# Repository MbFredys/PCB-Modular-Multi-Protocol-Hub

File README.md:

# ⚡ Universal Smart-Home Modular Hub  

A compact, scalable, multi-protocol communication platform designed for modern smart homes.  
Built around a powerful **ESP32-S3**, with plug-in radio modules for Zigbee/Thread and Proprietary RF.  
Reliable power architecture, clean RF design, and automatic module detection.

---

## 🌍 Overview  
This system uses a **three-board modular hub architecture**:

### **1) Main Board – ESP32-S3 Controller**
Contains the ESP32-S3 with native **Wi-Fi + Bluetooth LE**, full power management, Ethernet support, and the universal expansion bus.

### **2) Zigbee/Thread Module – EFR32MG24**
A dedicated 2.4 GHz radio module supporting **Zigbee**, **Thread**, and **Matter over Thread** with a high-efficiency antenna.

### **3) Proprietary RF Module – nRF24L01+**
A flexible low-power 2.4 GHz module for **custom protocols**, legacy devices, and private links.

⚠️ **Only one expansion module is active at a time.**  
The **Main Board can run standalone** using Wi-Fi and BLE even with no module attached.

---

## 🎯 Problem This Project Solves  
Most smart-home hubs are:

- Locked to one brand or protocol  
- Difficult to expand  
- Closed hardware  
- Not modifiable or repairable  
- Dependent on cloud services  
- Not designed for RF noise isolation  

This project solves these issues with a fully documented, open, modular, serviceable platform.

---

# 🚀 Main Features

---

## 🧠 Main Board – ESP32-S3 Core Controller  

### **Capabilities**
- Native Wi-Fi + BLE  
- USB programming  
- JTAG debugging  
- I²C bus for module identification  
- SPI bus shared with expansion modules  
- Presence-detect signal  
- Ethernet PHY  
- Local battery backup  
- Clean, isolated power rails  

### **Standalone Operation**
If no radio module is plugged in, the board still supports:

- Wi-Fi control  
- BLE provisioning  
- Local automation  
- OTA updates  

---

## 📡 Zigbee / Thread / Matter Module – EFR32MG24  

### **Capabilities**
- Zigbee 3.0  
- Thread 1.3  
- Matter over Thread  
- High-efficiency chip antenna or external u.FL  
- SPI + IRQ communication  
- Local low-noise LDO  
- EEPROM with module ID  
- Hardware reset & enable control  
- SWD header for development  

### **Why a Separate Board?**
- RF noise isolation  
- Easy upgrades  
- Thermal and EMI improvements  
- Lower main-board complexity  

---

## 📡 Proprietary RF Module – nRF24L01+  

### **Capabilities**
- 2.4 GHz bidirectional transceiver  
- SPI interface  
- IRQ line  
- CE line for TX/RX control  
- Local LDO for clean RF power  
- On-board EEPROM for identification  

### **Why It Exists**
- Legacy systems  
- Private, encrypted links  
- Ultra-low-power sensors  
- Custom protocols  

---

# 🔋 Power Architecture

### **Main Board**
- 12 V input  
- Step-down to 5 V  
- 3.3 V LDO for logic  
- Local LDOs for each RF module  
- Battery charger & backup  
- Inrush, surge, ESD protection  
- Proper decoupling everywhere  

### **Radio Modules**
- Dedicated LDO  
- Ferrite-bead power filtering  
- Enable pin for power control  
- RF-clean power domain  

---

# 🧩 Automatic Module Identification (EEPROM)

Every expansion module includes a **24AA02E48 EEPROM** that stores:

- Unique EUI-48  
- Module type ID  

The ESP32 reads the EEPROM via I²C on boot and:

1. Identifies the module type  
2. Powers only the selected module  
3. Loads the appropriate firmware configuration  

---

# 🛡️ Reliability & Safety

- TVS on power rails  
- ESD protection on connectors  
- Solid ground planes  
- RF-clean routing  
- Ferrite-bead domain separation  
- Reverse-polarity protection  
- Controlled RF impedance paths  

---

# 🧭 Why This Architecture Is Better

- **Fully modular** — plug-in radio modules  
- **Upgradable** — replace modules anytime  
- **Main board works standalone**  
- **Automatic detection** via EEPROM  
- **Clean RF design** with isolated power  
- **Open hardware**  
- **Supports Wi-Fi, BLE, Zigbee, Thread, Matter, Proprietary RF**  
- **Future-proof** platform  
- **Easy to manufacture & repair**  

---

# 🛠️ Usage

1. Power the Main Board with 12 V  
2. Plug in a Zigbee or Proprietary RF module  
3. Firmware reads the module EEPROM  
4. Selected module is powered via EN_LDO  
5. ESP32 configures SPI/I²C pins  
6. Start using the hub via Wi-Fi, BLE, or RF  

---

# 🚀 Getting Started

1. Download design files  
2. Open schematic and PCB in KiCad  
3. Review:
   - Power sections  
   - Module connector  
   - RF networks  
   - Decoupling and filtering  
4. Manufacture PCBs  
5. Assembly order:
   1. Power stage  
   2. ESP32-S3 main board  
   3. Expansion connectors  
   4. RF module components  
   5. Antennas  
6. Flash the ESP32-S3 via USB  
7. Flash EFR32 module via SWD (if needed)  
8. Test and integrate with your smart-home backend  

---

# 🪪 License  
This project is licensed under the CERN Open Hardware Licence Version 2 - Weakly Reciprocal (CERN-OHL-W-2.0).
See the [CERN-OHL-W-2.0 ↗](https://gitlab.com/ohwr/project/cernohl/-/wikis/uploads/82b567f43ce515395f7ddbfbad7a8806/cern_ohl_w_v2.txt) file for more information.

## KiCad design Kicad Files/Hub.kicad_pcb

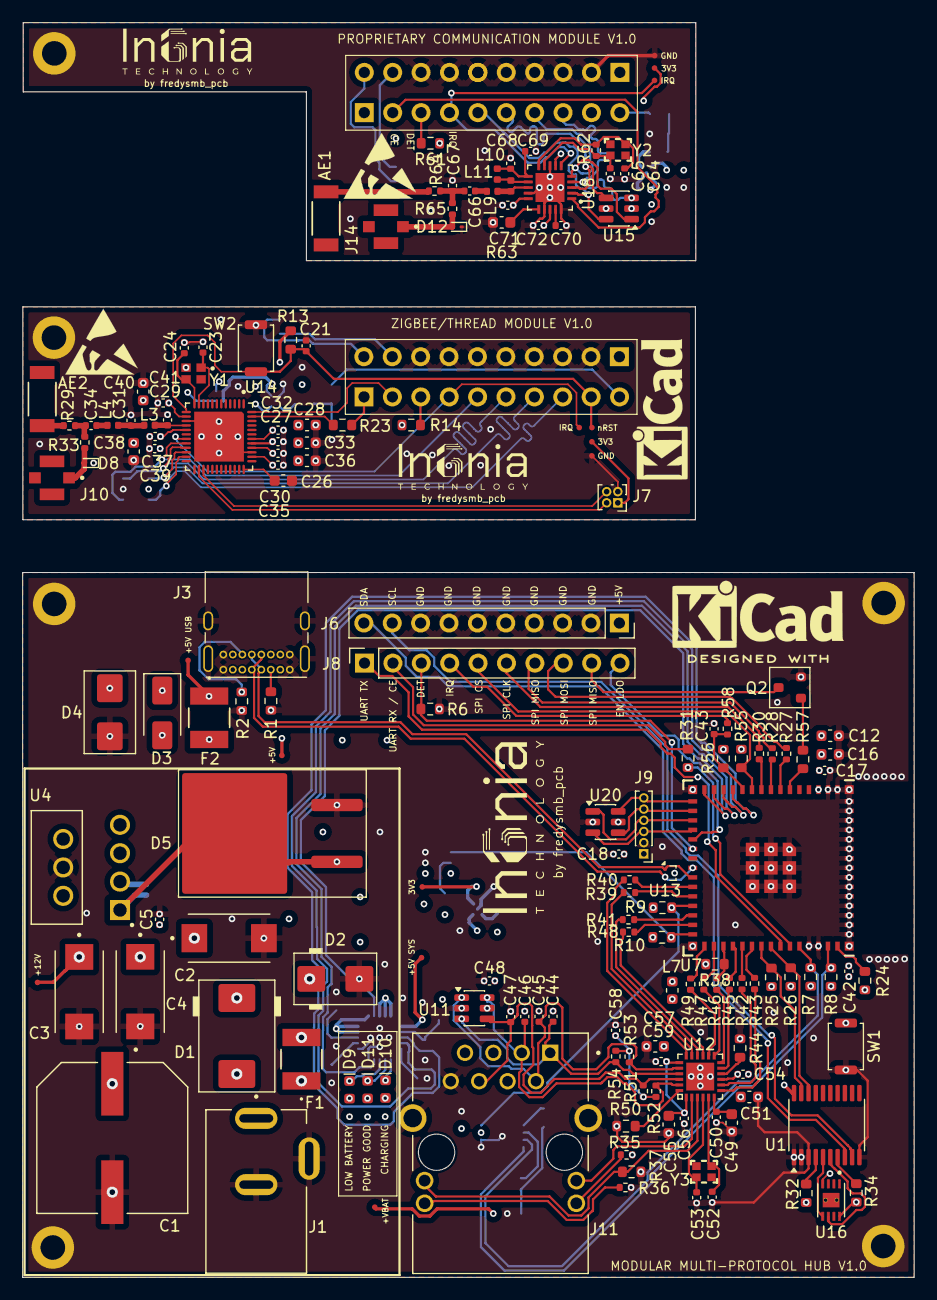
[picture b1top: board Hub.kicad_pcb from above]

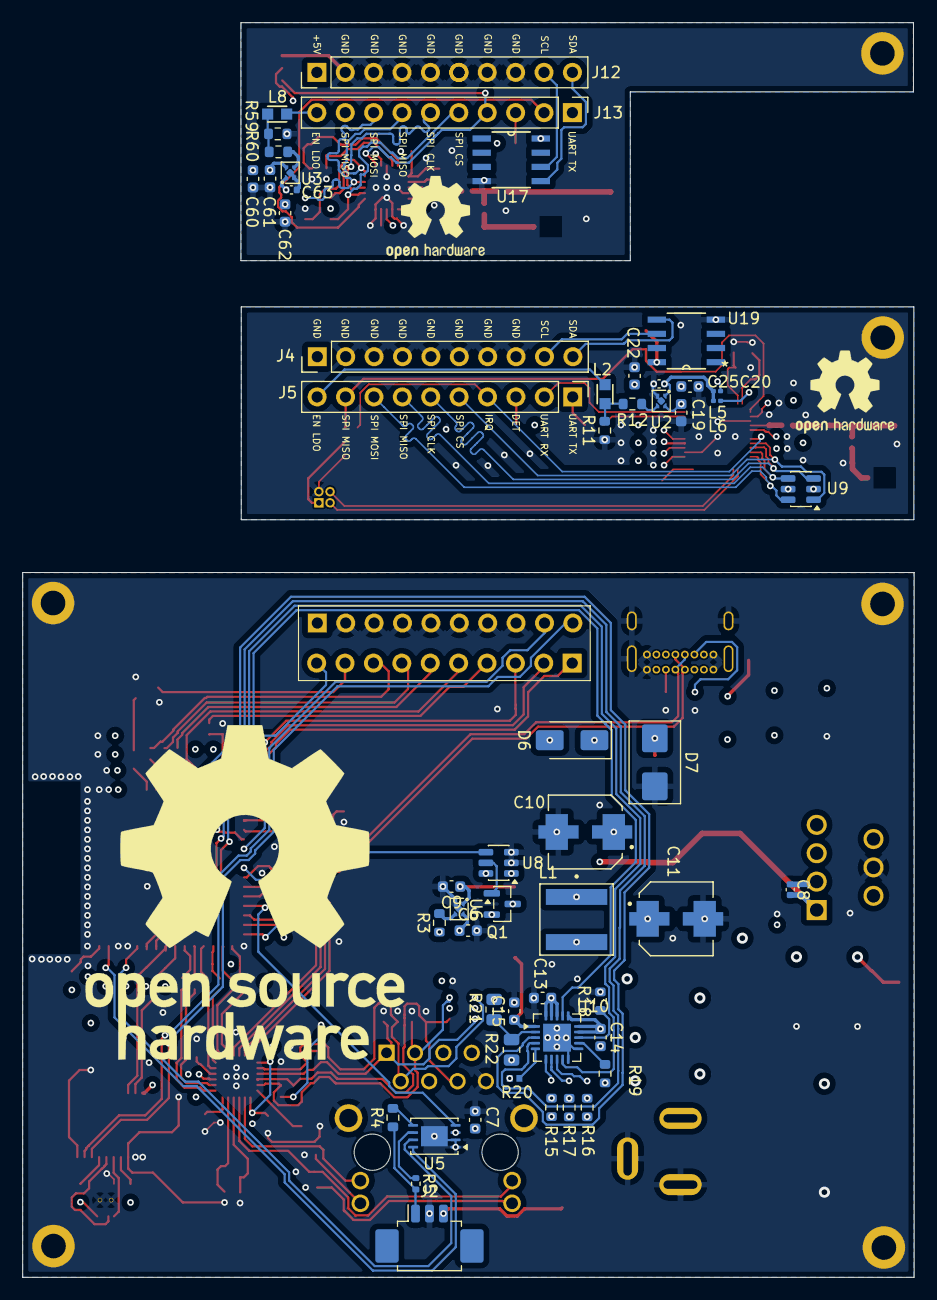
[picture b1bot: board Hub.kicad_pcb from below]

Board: 4 copper layers, 79.7 x 112.2 mm, 218 parts (54 on the bottom side), 159 nets.

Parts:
3V3, 3V3#2, 3V3#3: 0.5mm; TestPoint-0.5mm
+5V, +5V SYS, +5V USB, +12V: 0.5mm; TestPoint-0.5mm
+VBAT: 0.5mm; TestPoint-0.5mm
AE1, AE2: 2450AT42A100E; ANT_2450AT42A100E_JOT
C1: 1000uF; CAP_EEVFK1E102Q
C2, C3, C4: 15uF; CAPPM7343X310N
C5, C37: 0.47uF; C_0402_1005Metric
C6, C7, C9, C13, C16, C20, C22, C26, C28, C33, C36, C38, C49, C55, C57, C61, C62: 1uF; C_0603_1608Metric
C8: 0.01uF; C_0402_1005Metric
C10, C11: 180uF; CAP_EEEFNE181XUV
C12, C19, C51, C60: 10uF; C_0603_1608Metric
C14, C15: 4.7uF; C_0603_1608Metric
C17, C18, C21, C25, C27, C30, C32, C42, C43, C48, C54, C58, C63: 0.1uF; C_0402_1005Metric
C23, C24, C44, C45, C46, C47, C52, C53: 10pF; C_0402_1005Metric
C29: 2.3pF; C_0402_1005Metric
C31: 1.6pF; C_0402_1005Metric
C34, C41: 18pF; C_0402_1005Metric
C35, C69, C71: 10nF; C_0402_1005Metric
C39: 120pF; C_0402_1005Metric
C40: 2.2uF; C_0603_1608Metric
C50, C56, C59: 470pF; C_0402_1005Metric
C64, C65: 22pF; C_0402_1005Metric
C66: 1.5pF; C_0402_1005Metric
C67: 1pF; C_0402_1005Metric
C68, C70: 33nF; C_0402_1005Metric
C72: 1nF; C_0402_1005Metric
D1: SS54; D_SMC
D2: SMBJ12A; D_SMB
D3, D6: SS14; D_SMA
D4, D7: SMBJ5.0CA; D_SMB_TVS
D5: MBRB735; TO-263-2_TabPin1
D8, D12: ESD9B3.3ST5G; D_SOD-923
D9, D10, D11: LEDs; LED_0603_1608Metric
F1, F2: PTC_FUSE; FUSE_1812L05060_LTF
GND: 0.5mm; TestPoint-0.5mm
GND#2: 0.5mm; TestPoint-0.5mm
IRQ: 0.5mm; TestPoint-0.5mm
IRQ#2: 0.5mm; TestPoint-0.5mm
J1: CON_12VDC_IN; MPD_EJ503A
J2: Conn_BAT; Molex_PicoBlade_53261-0371_1x03-1MP_P1.25mm_Horizontal
J3: Conn_USB_C; USB_C_Receptacle_GCT_USB4085
J4, J5, J12, J13: PINHD; PinHeader_1x10_P2.54mm_Vertical
J6, J8: PINHD; PinSocket_1x10_P2.54mm_Vertical
J7: PINHD; PinHeader_2x02_P1.00mm_Vertical
J9: JTAG; PinHeader_1x06_P1.00mm_Vertical
J10, J14: CONMHF1; LINX_CONMHF1-SMD-G-T
J11: ARJM11D7-009-AB-EW2; ABRACON_ARJM11D7-009-AB-EW2
L1: 22uH; IND_XAL6060-223MEB
L2, L8: FerriteBead_0603_1.5A; R_0603
L3: 2.5nH; L_0402_1005Metric
L4: 1.7nH; L_0402_1005Metric
L5, L6: FerriteBead_0603_1.5A; R_0201_0603Metric
L7: FerriteBead; L_0603_1608Metric
L9: 3.9nH; L_0402_1005Metric
L10: 8.2nH; L_0402_1005Metric
L11: 2.7nH; L_0402_1005Metric
Q1: FDN340P; SOT-23
Q2: BC817; SOT-23
R1, R2: 5.1k; R_0603_1608Metric
R3, R6, R11, R59: 100k; R_0603_1608Metric
R4, R8, R9, R10, R12, R13, R14, R24, R37, R44, R55, R56, R57, R60, R61: 10k; R_0603_1608Metric
R5, R58: 100; R_0402_1005Metric
R7, R15, R16, R17, R18, R19: 470k; R_0603_1608Metric
R20: 10k; THRMC1005X55N
R21: 330k; R_0805_2012Metric
R22: 110k; R_0805_2012Metric
R23, R31: 1K; R_0603_1608Metric
R25, R26, R32, R34: 4.7k; R_0603_1608Metric
R27, R28, R30: 22; R_0402_1005Metric
R29, R33, R64, R65: 0; R_0402_1005Metric
R35, R36: 270; R_0402_1005Metric
R38: 2.2k; R_0603_1608Metric
R39, R40, R41, R42, R43, R45, R46, R47, R48, R49: 33; R_0402_1005Metric
R50: 12.1k; R_0603_1608Metric
R51, R52, R53, R54: 50; R_0402_1005Metric
R62: 1M; R_0402_1005Metric
R63: 22k; C_0603_1608Metric
SW1, SW2: uC_Reset; SW_Push_SPST_NO_Alps_SKRK
U1: TCA9544A; TSSOP-20_4.4x6.5mm_P0.65mm
U2, U3, U6: TPS7A20xxxDQN; Texas_X2SON-4_1x1mm_P0.65mm
U4: LM2678T-ADJ; TO127P1041X469X2199-7N
U5: LC709203FQH-01TWG; WDFN-8-1EP_4x3mm_P0.65mm_EP2.4x1.8mm
U7: ESP32-S3-MINI-1; ESP32-MINI
U8: LTC4412xS6; TSOT-23-6
U9, U11, U15, U20: WE-TVS-824015043; SOT-23-6
U10: MCP73871; QFN-20-1EP_4x4mm_P0.5mm_EP2.5x2.5mm
U12: LAN8720A
U13: TPD2EUSB30A; Texas_DRT-3
U14: EFR32MG24B310F1536IM48-B; XCVR_EFR32MG24B310F1536IM48-B
U16: ATECC608A-MAHDA-T; SON50P200X300X60-9N
U17, U19: 24AA02E48-I_SN; SOIC127P600X175-8N
U18: NRF24L01; QFN50P400X400X95-21N
Y1: 39MHz; XTAL_ECS-390-CDX-1932
Y2: 16MHz; Crystal_SMD_2.0x1.6mm
Y3: 25MHz; Crystal_SMD_2.0x1.6mm
nRST: 0.5mm; TestPoint-0.5mm

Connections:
+3V3_Main: 3V3#3.1, C9.1, C12.2, C16.1, C17.2, C18.2, C42.2, C48.2, C51.2, C54.2, J9.1, J11.4 (CT1), J11.5 (CT2), L7.1, R7.1, R8.1, R9.1, R10.1, R24.2, R25.1, R26.1, R32.1, R34.1, R38.2, R55.2, R56.2, SW1.2, U1.20 (VCC), U6.1 (OUT), U7.3 (3V3), U11.5 (VBUS), U12.9 (VDDIO), U16.8 (VCC), U20.5 (VBUS)
+3V3_PROP: 3V3.1, C62.1, C63.2, C71.2, C72.2, R61.1, U3.1 (OUT), U15.5 (VBUS), U17.8 (VCC), U18.7 (VDD), U18.15 (VDD), U18.18 (VDD)
+3V3_ZGB: 3V3#2.1, C22.1, C25.2, C27.2, C28.1, C30.2, C32.2, C33.1, C35.2, C36.1, J7.1, L5.1, L6.1, R13.1, R14.1, U2.1 (OUT), U9.5 (VBUS), U14.38 (VREGVDD), U14.40 (DVDD), U14.41 (AVDD), U14.42 (IOVDD), U19.8 (VCC)
+5V: +5V.1, +5V SYS.1, C6.1, C13.1, C15.1, D3.1 (K), D4.2 (A), D6.1 (K), D7.2 (A), J6.1, Q1.2 (S), R3.1, R15.1, R16.1, R17.1, R21.1, U6.4 (IN), U8.6 (SENSE), U10.1 (OUT), U10.18 (IN), U10.19 (IN), U10.20 (OUT)
+5V_PROP: C60.2, C61.1, J12.1, U3.4 (IN)
+5V_ZGB: C19.2, C20.1, J4.1, U2.4 (IN)
+12V: +12V.1, C1.1, C2.1, C3.1, C4.1, C5.1, D1.1 (K), D2.1 (K), U4.2 (INPUT), U4.7 (ON/~OFF)
+V_BAT: +VBAT.1, C7.1, C14.1, J2.3, Q1.3 (D), U5.3 (V_{DD}), U8.1 (VIN), U10.14 (V_{BAT}), U10.15 (V_{BAT}), U10.16 (V_{BAT_SENSE})
/Main Board/Ethernet/ESP32/LAN87_CRS_DV: R45.1, U7.34 (IO38)
/Main Board/Ethernet/ESP32/LAN87_MDC: R47.1, U7.32 (IO36)
/Main Board/Ethernet/ESP32/LAN87_MDIO: R38.1, R46.1, U7.33 (IO37)
/Main Board/Ethernet/ESP32/LAN87_REFCLKO: R49.1, U7.31 (IO35)
/Main Board/Ethernet/ESP32/LAN87_RXD0: R42.1, U7.35 (IO39)
/Main Board/Ethernet/ESP32/LAN87_RXD1: R43.1, U7.36 (IO40)
/Main Board/Ethernet/ESP32/LAN87_TXD0: R39.1, U7.26 (IO26)
/Main Board/Ethernet/ESP32/LAN87_TXD1: R40.1, U7.25 (IO21)
/Main Board/Ethernet/ESP32/LAN87_TXEN: R41.1, U7.28 (IO33)
/Main Board/Ethernet/ESP32/LAN87_nRST: R48.1, U7.29 (IO34)
/Main Board/Ethernet/LAN87/RJ45_LED1: J11.9, R37.2, U12.3 (LED1/REGOFF)
/Main Board/Ethernet/LAN87/RJ45_LED2: J11.11, U12.2 (LED2/~INTSEL)
/Main Board/Ethernet/LAN87/RJ45_RX+: C46.1, J11.3 (RD+), R52.2, U11.6 (I/O4), U12.23 (RXP)
/Main Board/Ethernet/LAN87/RJ45_RX-: C47.1, J11.6 (RD-), R51.2, U11.4 (I/O3), U12.22 (RXN)
/Main Board/Ethernet/LAN87/RJ45_TX+: C44.1, J11.1 (TD+), R54.2, U11.3 (I/O2), U12.21 (TXP)
/Main Board/Ethernet/LAN87/RJ45_TX-: C45.1, J11.2 (TD-), R53.2, U11.1 (I/O1), U12.20 (TXN)
/Main Board/MainB_CTRL/CE_ESP32/MCP73871: U7.15 (IO11), U10.17 (CE)
/Main Board/MainB_CTRL/EN_LDO: J8.10, U7.20 (IO16)
/Main Board/MainB_CTRL/ESP32/USB_D+: J3.A6 (D+), J3.B6 (D+), U7.24 (USB_D+), U13.1 (D+)
/Main Board/MainB_CTRL/ESP32/USB_D-: J3.A7 (D-), J3.B7 (D-), U7.23 (USB_D-), U13.2 (D-)
/Main Board/MainB_CTRL/I2C_SCL_ATECCC60: U1.6 (SC0), U16.6 (SCL)
/Main Board/MainB_CTRL/I2C_SCL_EEPROM: J6.9, U1.9 (SC1)
/Main Board/MainB_CTRL/I2C_SCL_LC7092/ESP32: R8.2, U5.8 (SCL), U7.44 (IO46)
/Main Board/MainB_CTRL/I2C_SCL_TCA95/ESP32: R26.2, U1.18 (SCL), U7.38 (IO42)
/Main Board/MainB_CTRL/I2C_SDA_ATECCC60: U1.5 (SD0), U16.5 (SDA)
/Main Board/MainB_CTRL/I2C_SDA_EEPROM: J6.10, U1.8 (SD1)
/Main Board/MainB_CTRL/I2C_SDA_LC7092/ESP32: R7.2, U5.7 (SDA), U7.41 (IO45)
/Main Board/MainB_CTRL/I2C_SDA_TCA95/ESP32: R25.2, U1.19 (SDA), U7.37 (IO41)
/Main Board/MainB_CTRL/INT_LC7092/ESP32: R9.2, U5.4 (~ALARMB), U7.27 (IO47)
/Main Board/MainB_CTRL/IRQ: J8.4, R58.1
/Main Board/MainB_CTRL/JTAG_TCK: J9.6, U7.16 (IO12), U20.6 (I/O4)
/Main Board/MainB_CTRL/JTAG_TDI: J9.4, U7.18 (IO14), U20.1 (I/O1)
/Main Board/MainB_CTRL/JTAG_TDO: J9.3, U7.19 (IO15), U20.3 (I/O2)
/Main Board/MainB_CTRL/JTAG_TMS: J9.5, U7.17 (IO13), U20.4 (I/O3)
/Main Board/MainB_CTRL/PRESENCE_DET: J8.3, R6.2, U7.21 (IO17)
/Main Board/MainB_CTRL/PWR_SEL_ESP32/MCP73871: U7.12 (IO8), U10.3 (SEL)
/Main Board/MainB_CTRL/SPI_CLK: J8.6, R30.2
/Main Board/MainB_CTRL/SPI_CS: J8.5, R55.1, U7.10 (IO6)
/Main Board/MainB_CTRL/SPI_MISO: J8.7, R28.2
/Main Board/MainB_CTRL/SPI_MOSI: J8.8, R27.1
/Main Board/MainB_CTRL/STATE_LTC4412/ESP32: R10.2, U7.30 (IO48), U8.4 (STAT)
/Main Board/MainB_CTRL/TIMER_ESP32/MCP73871: U7.14 (IO10), U10.9 (~TE)
/Main Board/MainB_CTRL/UART_RX / CE: J8.2, R31.1
/Main Board/MainB_CTRL/UART_TX: J8.1, U7.39 (TXD0)
/Main Board/MainB_CTRL/USB_ISEL_ESP32/MCP73871: U7.13 (IO9), U10.4 (PROG2)
/Main Board/MainB_CTRL/nRST: J8.9, Q2.3 (C)
/Main Board/MainB_PWR/BAT_Temp: J2.1, R4.1, R5.2
/Proprietary Communication Module/EN_LDO_PROP: J13.10, L8.1
/Proprietary Communication Module/I2C_SCL_24AA02_PROP: J12.9, U17.6 (SCL)
/Proprietary Communication Module/I2C_SDA_24AA02_PROP: J12.10, U17.5 (SDA)
/Proprietary Communication Module/IRQ_ESP32/NRF24L01: IRQ#2.1, J13.4, U18.6 (~IRQ)
/Proprietary Communication Module/PRESENCE_DET_ESP32/NRF24L01: J13.3, R61.2
/Proprietary Communication Module/SPI_ESP32/NRF24L01_CE: J13.2, U18.1 (CE)
/Proprietary Communication Module/SPI_ESP32/NRF24L01_CLK: J13.6, U15.4 (I/O3), U18.3 (SCK)
/Proprietary Communication Module/SPI_ESP32/NRF24L01_CS: J13.5, U15.6 (I/O4), U18.2 (CSN)
/Proprietary Communication Module/SPI_ESP32/NRF24L01_MISO: J13.7, U15.1 (I/O1), U18.5 (MISO)
/Proprietary Communication Module/SPI_ESP32/NRF24L01_MOSI: J13.8, U15.3 (I/O2), U18.4 (MOSI)
/Zigbee-Thread Module/EN_LDO_Zigbee/Thread: J5.10, L2.1
/Zigbee-Thread Module/I2C_SCL_24AA02_ZGB: J4.9, U19.6 (SCL)
/Zigbee-Thread Module/I2C_SDA_24AA02_ZGB: J4.10, U19.5 (SDA)
/Zigbee-Thread Module/IRQ_ESP32/EFR32MG24: IRQ.1, J5.4, U14.19 (PB04)
/Zigbee-Thread Module/PRESENCE_DET_ESP32/EFR32MG24: J5.3, R14.2
/Zigbee-Thread Module/PROG_SWCLK: J7.2, U14.26 (PA00)
/Zigbee-Thread Module/PROG_SWDIO: J7.4, U14.27 (PA01)
/Zigbee-Thread Module/SPI_ESP32/EFR32MG24_CLK: J5.6, U9.3 (I/O2), U14.21 (PB02)
/Zigbee-Thread Module/SPI_ESP32/EFR32MG24_CS: J5.5, U9.1 (I/O1), U14.20 (PB03)
/Zigbee-Thread Module/SPI_ESP32/EFR32MG24_MISO: J5.7, U9.4 (I/O3), U14.22 (PB01)
/Zigbee-Thread Module/SPI_ESP32/EFR32MG24_MOSI: J5.8, U9.6 (I/O4), U14.23 (PB00)
/Zigbee-Thread Module/UART_RX_ESP32/EFR32MG24: J5.1, R23.1
/Zigbee-Thread Module/UART_TX_ESP32/EFR32MG24: J5.2, U14.48 (PD00)
/Zigbee-Thread Module/nRST_ESP32/EFR32MG24: C21.2, J5.9, R13.2, SW2.2, U14.13 (~RESET), nRST.1
GND: C1.2, C2.2, C3.2, C4.2, C5.2, C6.2, C7.2, C9.2, C10.2, C11.2, C12.1, C13.2, C14.2, C15.2, C16.2, C17.1, C18.1, C19.1, C20.2, C21.1, C22.2, C23.1, C24.1, C25.1, C26.1, C27.1, C28.2, C29.1, C30.1, C31.1, C32.1, C33.2, C35.1, C36.2, C37.1, C38.2, C39.1, C40.1, C41.1, C42.1, C43.1, C44.2, C45.2, C46.2, C47.2, C48.1, C49.2, C50.2, C51.1, C52.1, C53.1, C54.1, C55.2, C56.2, C57.2, C58.1, C59.2, C60.1, C61.2, C62.2, C63.1, C64.1, C65.1, C67.1, C68.1, C69.1, C70.1, C71.1, C72.1, D2.2 (A), D4.1 (K), D5.2 (A), D7.1 (K), D8.1 (A1), D12.1 (A1), GND.1, GND#2.1, J1.2, J1.3, J2.2, J3.A1 (GND), J3.A12 (GND), J3.B1 (GND), J3.B12 (GND), J3.S1 (SHIELD), J4.2, J4.3, J4.4, J4.5, J4.6, J4.7, J4.8, J6.2, J6.3, J6.4, J6.5, J6.6, J6.7, J6.8, J7.3, J9.2, J11.8 (GND), J11.SH1 (SHIELD), J11.SH2 (SHIELD), J12.2, J12.3, J12.4, J12.5, J12.6, J12.7, J12.8, Q2.2 (E), R1.2, R2.2, R6.1, R11.1, R18.2, R19.2, R20.1, R22.2, R35.2, R36.2, R37.1, R44.2, R50.1, R59.1, R63.1, SW1.1, SW2.1, U1.1 (A0), U1.2 (A1), U1.3 (A2), U1.10 (GND), U2.2 (GND), U2.5 (Pad), U3.2 (GND), U3.5 (Pad), U4.4 (GND), U5.1 (TEST), U5.2 (V_{SS}), U5.9 (EP), U6.2 (GND), U6.5 (Pad), U7.1 (GND), U7.2 (GND), U7.42 (GND), U7.43 (GND), U7.46 (GND), U7.47 (GND), U7.48 (GND), U7.49 (GND), U7.50 (GND), U7.51 (GND), U7.52 (GND), U7.53 (GND), U7.54 (GND), U7.55 (GND), U7.56 (GND), U7.57 (GND), U7.58 (GND), U7.59 (GND), U7.60 (GND), U7.61 (GND), U7.62 (GND), U7.63 (GND), U7.64 (GND), U7.65 (GND), U8.2 (GND), U8.3 (CTL), U9.2 (GND), U10.10 (V_{SS}), U10.11 (V_{SS}), U10.21 (V_{SS}), U11.2 (GND), U12.25 (VSS), U13.3 (GND), U14.15 (RFVSS), U14.39 (VREGVSS), U14.49 (VSS), U15.2 (GND), U16.4 (GND), U16.9 (EXP), U16.9_1 (EXP), U16.9_2 (EXP), U17.4 (VSS), U18.8 (VSS), U18.14 (VSS), U18.17 (VSS), U18.20 (VSS), U18.21 (EP), U19.4 (VSS), U20.2 (GND), Y1.2
unnamed: AE1.1, R64.2
unnamed: AE2.1, R29.2
unnamed: C31.2, L3.2, L4.1
unnamed: C34.1, R29.1, R33.1
unnamed: C34.2, L4.2
unnamed: C58.2, R51.1, R52.1, R53.1, R54.1
unnamed: C66.1, C67.2, R64.1, R65.1
unnamed: C66.2, L9.2
unnamed: D1.2 (A), F1.2
unnamed: D3.2 (A), F2.2
unnamed: C8.2, D5.1 (K), L1.1, U4.1 (SWITCH_OUTPUT)
unnamed: C10.1, C11.1, D6.2 (A), L1.2, U4.6 (FB)
unnamed: D8.2 (A2), J10.1 (In), R33.2
unnamed: D9.2 (A), R16.2
unnamed: D9.1 (K), U10.8 (STAT1/~LBO)
unnamed: D10.2 (A), R15.2
unnamed: D10.1 (K), U10.6 (~PG)
unnamed: D11.2 (A), R17.2
unnamed: D11.1 (K), U10.7 (STAT2)
unnamed: D12.2 (A2), J14.1 (In), R65.2
unnamed: F1.1, J1.1
unnamed: +5V USB.1, F2.1, J3.A4 (VBUS), J3.A9 (VBUS), J3.B4 (VBUS), J3.B9 (VBUS)
unnamed: J3.A5 (CC1), R1.1
unnamed: J3.B5 (CC2), R2.1
unnamed: J11.10, R36.1
unnamed: J11.12, R35.1
unnamed: L2.2, R11.2, R12.2
unnamed: L8.2, R59.2, R60.2
unnamed: Q1.1 (G), U8.5 (GATE)
unnamed: Q2.1 (B), R57.2
unnamed: R32.2, U1.4 (~INT0)
unnamed: R34.2, U1.7 (~INT1)
unnamed: R12.1, U2.3 (EN)
unnamed: R60.1, U3.3 (EN)
unnamed: C8.1, U4.3 (CB)
unnamed: R5.1, U5.6 (T_{SENSE})
unnamed: R4.2, U5.5 (T_{SW})
unnamed: R3.2, U6.3 (EN)
unnamed: R24.1, U7.45 (EN)
unnamed: R57.1, U7.6 (IO2)
unnamed: R27.2, U7.7 (IO3)
unnamed: R28.1, U7.8 (IO4)
unnamed: R30.1, U7.9 (IO5)
unnamed: C43.2, R56.1, R58.2, U7.11 (IO7)
unnamed: R31.2, U7.40 (RXD0)
unnamed: R18.1, U10.13 (PROG1)
unnamed: R19.1, U10.12 (PROG3)
unnamed: R20.2, U10.5 (THERM)
unnamed: R21.2, R22.1, U10.2 (VPCC)
unnamed: R45.2, U12.11 (CRS_DV/MODE2)
unnamed: R47.2, U12.13 (MDC)
unnamed: R46.2, U12.12 (MDIO)
unnamed: R50.2, U12.24 (RBIAS)
unnamed: R42.2, U12.8 (RXD0/MODE0)
unnamed: R43.2, U12.7 (RXD1/MODE1)
unnamed: R44.1, U12.10 (RXER/PHYAD0)
unnamed: R39.2, U12.17 (TXD0)
unnamed: R40.2, U12.18 (TXD1)
unnamed: R41.2, U12.16 (TXEN)
unnamed: C55.1, C56.1, C57.1, C59.1, L7.2, U12.1 (VDD2A), U12.19 (VDD1A)
unnamed: C49.1, C50.1, U12.6 (VDDCR)
unnamed: C52.2, U12.5 (XTAL1/CLKIN), Y3.1
unnamed: C53.2, U12.4 (XTAL2), Y3.2
unnamed: R49.2, U12.14 (~INT/REFCLKO)
unnamed: R48.2, U12.15 (~RST)
unnamed: C26.2, U14.36 (DECOUPLE)
unnamed: C23.2, U14.11 (HFXTAL_I), Y1.1
unnamed: C24.2, U14.12 (HFXTAL_O), Y1.3
unnamed: C37.2, C38.1, C39.2, L5.2, U14.17 (PAVDD)
unnamed: R23.2, U14.47 (PD01)
unnamed: C29.2, L3.1, U14.16 (RF2G4_IO)
unnamed: C40.2, C41.2, L6.2, U14.14 (RFVDD)
unnamed: L10.2, L11.1, U18.12 (ANT1)
unnamed: L9.1, L10.1, U18.13 (ANT2)
unnamed: C70.2, U18.19 (DVDD)
unnamed: R63.2, U18.16 (IREF)
unnamed: C68.2, C69.2, L11.2, U18.11 (VDD_PA)
unnamed: C64.2, R62.2, U18.10 (XC1), Y2.1
unnamed: C65.2, R62.1, U18.9 (XC2), Y2.2

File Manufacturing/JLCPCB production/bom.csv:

Designator,Footprint,Quantity,Value,LCSC Part #
"_6, _5, _4, _3, _2, ",,6,,
"+12V, +5V, +5V SYS, +5V USB, +VBAT, 3V3_3, 3V3_2, 3V3, GND_2, GND, IRQ_2, IRQ, NRST",TestPoint-0.5mm,13,0.5mm,
"AE1, AE2",ANT_2450AT42A100E_JOT,2,2450AT42A100E,C2917719
C1,CAP_EEVFK1E102Q,1,1000uF,C178725
"C10, C11",CAP_EEEFNE181XUV,2,180uF,C540948
"C12, C51",0603,2,10uF,C48579265
"C13, C16, C20, C22, C26, C28, C33, C36, C38, C49, C55, C57, C6, C61, C62, C7, C9",0603,17,1uF,C15849
"C14, C15",0603,2,4.7uF,C1705
"C17, C18, C21, C25, C27, C30, C32, C42, C43, C48, C54, C58, C63",0402,13,0.1uF,C48579249
"C19, C60",0603,2,10uF,C15849
"C2, C3, C4",CAPPM7343X310N,3,15uF,C382110
"C23, C24, C44, C45, C46, C47, C52, C53",0402,8,10pF,C106199
C29,0402,1,2.3pF,C2220993
C31,0402,1,1.6pF,C161311
"C34, C41",0402,2,18pF,C106202
"C35, C69, C71",0402,3,10nF,CL05B103KB5NNNC
C37,0402,1,0.47uF,C92361
C39,0402,1,120pF,C106996
C40,0603,1,2.2uF,C48579298
C5,0402,1,0.47uF,C471404
"C50, C59",0402,2,470pF,C76971
C56,0402,1,470pF,
"C64, C65",0402,2,22pF,C76960
C66,0402,1,1.5pF,C76901
C67,0402,1,1pF,C76898
"C68, C70",0402,2,33nF,C7419416
C72,0402,1,1nF,C77018
C8,0402,1,0.01uF,C5137480
D1,D_SMC,1,SS54,C22452
"D10, D11, D9",0603,3,LEDs,C19171301
"D12, D8",D_SOD-923,2,ESD9B3.3ST5G,C96512
D2,D_SMB,1,SMBJ12A,C151251
"D3, D6",D_SMA,2,SS14,C2837270
"D4, D7",D_SMB_TVS,2,SMBJ5.0CA,C5331095
D5,TO-263-2_TabPin1,1,MBRB735,C6604203
"F1, F2",FUSE_1812L05060_LTF,2,PTC_FUSE,C163516
J1,MPD_EJ503A,1,CON_12VDC_IN,C3095117
"J10, J14",LINX_CONMHF1-SMD-G-T,2,CONMHF1,C22442695
J11,ABRACON_ARJM11D7-009-AB-EW2,1,ARJM11D7-009-AB-EW2,C3179097
"J12, J13",PinHeader_1x10_P2.54mm_Vertical,2,PINHD,
J2,Molex_PicoBlade_53261-0371_1x03-1MP_P1.25mm_Horizontal,1,Conn_BAT,C293630
J3,USB_C_Receptacle_GCT_USB4085,1,Conn_USB_C,C7095263
"J4, J5",PinHeader_1x10_P2.54mm_Vertical,2,PINHD,C492409
"J6, J8",PinSocket_1x10_P2.54mm_Vertical,2,PINHD,C5444407
J7,PinHeader_2x02_P1.00mm_Vertical,1,PINHD,C225517
J9,PinHeader_1x06_P1.00mm_Vertical,1,JTAG,C52016393
L1,IND_XAL6060-223MEB,1,22uH,C475917
L10,0402,1,8.2nH,C84404
L11,0402,1,2.7nH,C162541
"L2, L8",R_0603,2,FerriteBead_0603_1.5A,C2442094
L3,0402,1,2.5nH,C237342
L4,0402,1,1.7nH,C237342
"L5, L6",0201,2,FerriteBead_0603_1.5A,C97850
L7,0603,1,FerriteBead,C14709
L9,0402,1,3.9nH,C98062
Q1,SOT-23,1,FDN340P,C75469
Q2,SOT-23,1,BC817,C609806
"R1, R2",0603,2,5.1k,C2907114
"R10, R12, R13, R14, R24, R37, R4, R44, R55, R56, R57, R60, R8, R9",0603,14,10k,C2906982
"R11, R3, R59, R6",0603,4,100k,C2906980
"R15, R16, R17, R18, R19, R7",0603,6,470k,C2930293
R20,THRMC1005X55N,1,10k,C17294780
R21,0805,1,330k,C2907257
R22,0805,1,110k,C2907221
"R23, R31",0603,2,1K,C49196685
"R25, R26, R32, R34",0603,4,4.7k,C2907034
"R27, R28, R30",0402,3,22,C2929994
"R29, R33, R64, R65",0402,4,0,C106231
R38,0603,1,2.2k,C114662
"R39, R40, R41, R42, R43, R45, R46, R47, R48, R49",0402,10,33,C2906868
"R5, R58",0402,2,100,C2906860
R50,0603,1,12.1k,C2930059
"R51, R52, R53, R54",0402,4,50,C853312
R61,0603,1,10k,
R62,0402,1,1M,C138033
R63,0603,1,22k,C2907015
"SW1, SW2",SW_Push_SPST_NO_Alps_SKRK,2,uC_Reset,C115357
U1,TSSOP-20_4.4x6.5mm_P0.65mm,1,TCA9544A,C2674619
U10,QFN-20-1EP_4x4mm_P0.5mm_EP2.5x2.5mm,1,MCP73871,C5121473
U11,SOT-23-6,1,WE-TVS-824015043,824015043
U12,LAN8720A,1,LAN8720A,C17146
U13,Texas_DRT-3,1,TPD2EUSB30A,C94934
U14,XCVR_EFR32MG24B310F1536IM48-B,1,EFR32MG24B310F1536IM48-B,C6033379
"U15, U20, U9",SOT-23-6,3,WE-TVS-824015043,
U16,SON50P200X300X60-9N,1,ATECC608A-MAHDA-T,C4749250
"U17, U19",SOIC127P600X175-8N,2,24AA02E48-I_SN,C81475
U18,QFN50P400X400X95-21N,1,NRF24L01,C7015539
"U2, U3, U6",Texas_X2SON-4_1x1mm_P0.65mm,3,TPS7A20xxxDQN,C2866482
U4,TO127P1041X469X2199-7N,1,LM2678T-ADJ,C95178
U5,WDFN-8-1EP_4x3mm_P0.65mm_EP2.4x1.8mm,1,LC709203FQH-01TWG,C152311
U7,ESP32-MINI,1,ESP32-S3-MINI-1,C2913206
U8,TSOT-23-6,1,LTC4412xS6,C514442
Y1,XTAL_ECS-390-CDX-1932,1,39MHz,C19858547
Y2,Crystal_SMD_2.0x1.6mm,1,16MHz,C1985805
Y3,Crystal_SMD_2.0x1.6mm,1,25MHz,C1985948

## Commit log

2025-11-30 Revise README for Universal Smart-Home Modular Hub
    Updated project description and added detailed features and architecture information.
2025-11-30 Add initial firmware documentation placeholder
2025-11-30 Create kicad
2025-11-30 Add fabrication files documentation
2025-11-30 Update schematic.md to add header
2025-11-30 Add section header for 3D Views
2025-12-01 Change license from MIT to CERN OHL v2
2025-12-01 Change license from MIT to CERN-OHL-W-2.0
    Updated license information in README.
2025-12-01 Add CERN Open Hardware Licence Version 2
    This file contains the CERN Open Hardware Licence Version 2 - Weakly Reciprocal, outlining the terms for using, modifying, and distributing covered source and products.
2025-12-01 Fix link to CERN-OHL-W-2.0 license
2025-12-01 Fix license link in LICENSE file
    Updated the link to the CERN-OHL-W v2 license text.

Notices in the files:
README.md:
License: CERN-OHL-W-2.0
